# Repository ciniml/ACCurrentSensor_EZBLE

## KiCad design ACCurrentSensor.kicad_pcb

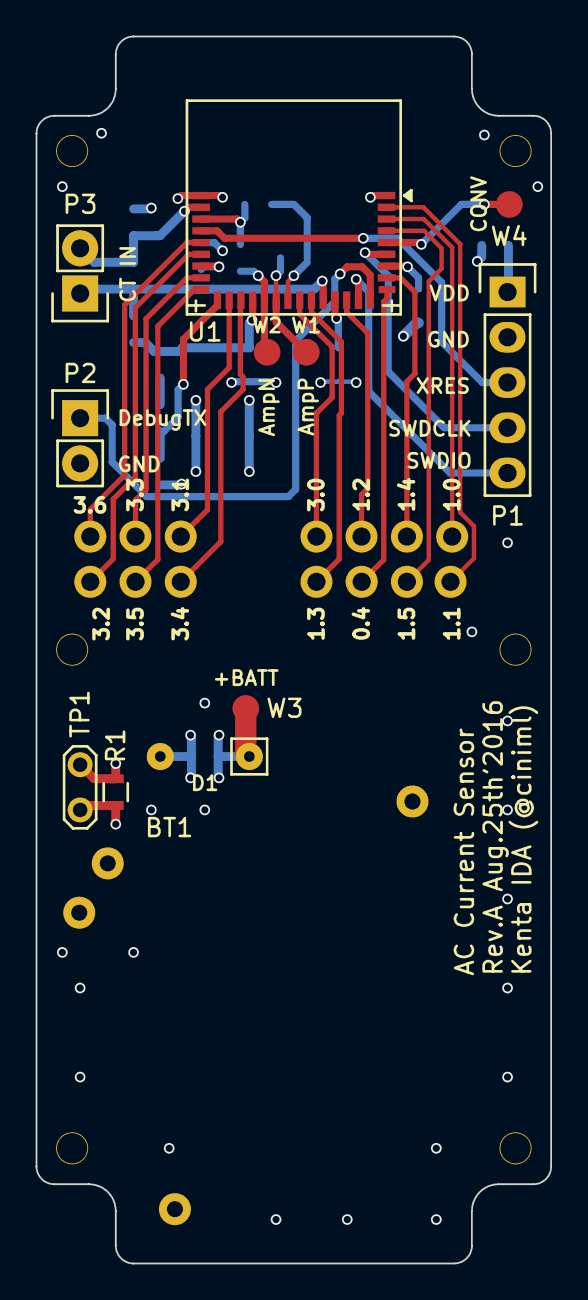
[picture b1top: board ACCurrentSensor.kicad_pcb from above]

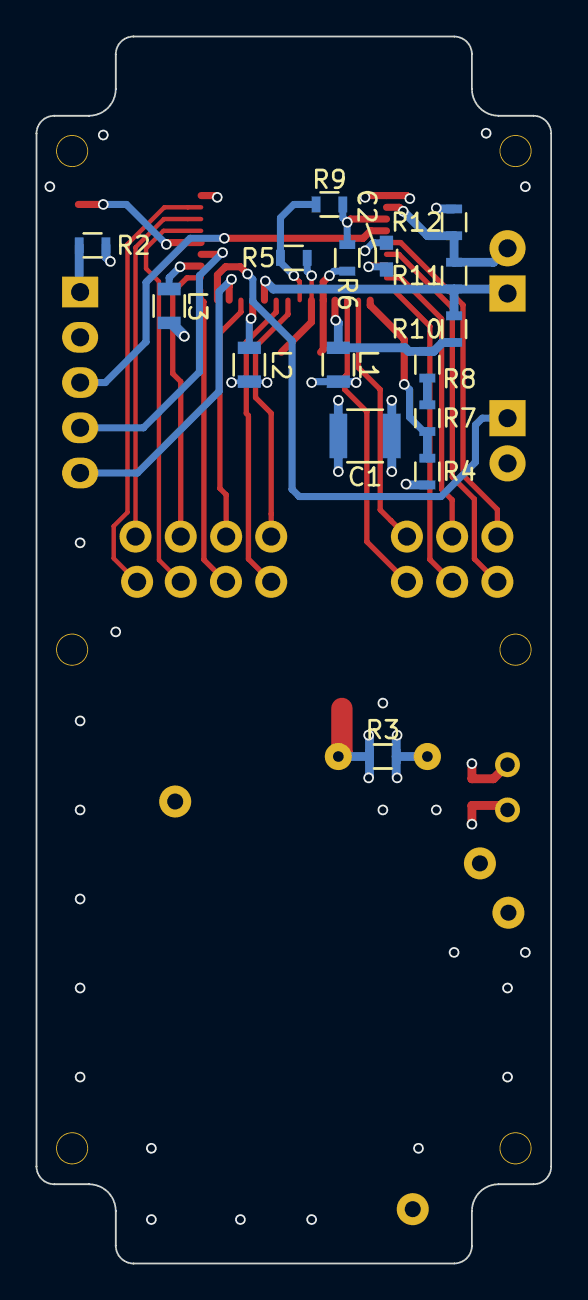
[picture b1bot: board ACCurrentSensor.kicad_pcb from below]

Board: 4 copper layers, 28.9 x 68.9 mm, 42 parts (16 on the bottom side), 36 nets.

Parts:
BT1: Battery; CSPB-75
C1: 100u; C_1210
C2: 100n; C_0603
D1: E-452; CRD-E
L1, L2, L3: BLM21PG331SN; R_0805
P1: PROG; Pin_Header_Straight_1x05
P2: DEBUG_TX; Pin_Header_Straight_1x02
P3: CT; Pin_Header_Straight_1x02
P4, P5, P6, P7, P8, P9, P10, P11, P12, P13, P14, P15, P16, P17: CONN_01X01; OptionalPad_TH
R1, R2, R3: 0R; R_0603
R4, R7, R8, R10, R12: 100k; R_0603
R5, R6: 10k; R_0603
R9: 2k; R_0603
R11: 10; R_0603
TP1: CURRENT; Test_Point_2Pads
U1: CYBLE-014008-00
W1: SENSE_OUT_P; Measurement_Point_Round-SMD-Pad_Small
W2: SENSE_OUT_N; Measurement_Point_Round-SMD-Pad_Small
W3: BATT; Measurement_Point_Round-SMD-Pad_Small
W4: CONVERTED; Measurement_Point_Round-SMD-Pad_Small

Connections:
+BATT: C1.1, D1.K, L1.1, L2.1, L3.1, R2.2, R3.2, W3.1
/BATTREF: R4.2, R7.2, U1.23
/CONVERTED: U1.5, W4.1
/DebugTX: P2.1, U1.10
/OA_H_N: R5.1, R9.2, U1.17
/OA_H_OUT: R5.2, U1.18, W1.1
/OA_H_P: P3.1, R10.1, R11.2, U1.14
/OA_L_N: P3.2, R11.1, R12.2, U1.31
/OA_L_OUT: R6.2, U1.19, W2.1
/OA_L_P: R6.1, R9.1, U1.30
/PIN_0.4: P8.1, U1.9
/PIN_1.0: P5.1, U1.3
/PIN_1.1: P4.1, U1.2
/PIN_1.2: P9.1, U1.12
/PIN_1.3: P10.1, U1.15
/PIN_1.4: P7.1, U1.8
/PIN_1.5: P6.1, U1.4
/PIN_3.0: P11.1, U1.16
/PIN_3.1: P13.1, U1.22
/PIN_3.2: P17.1, U1.27
/PIN_3.3: P14.1, U1.25
/PIN_3.4: P12.1, U1.21
/PIN_3.5: P15.1, U1.24
/PIN_3.6: P16.1, U1.28
/SWDCLK: P1.4, U1.6
/SWDIO: P1.5, U1.11
/XRES: P1.3, U1.29
GND: BT1.2, C1.2, C2.2, P1.2, P2.2, R4.1, R12.1, U1.1, U1.32
unnamed: BT1.1, R1.1, TP1.1
unnamed: C2.1, U1.26
unnamed: D1.A, R1.2, R3.1, TP1.2
unnamed: L2.2, U1.13
unnamed: P1.1, R2.1
unnamed: R7.1, R8.2
VDD: L3.2, U1.7
VDDA: L1.2, R8.1, R10.2, U1.20

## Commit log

2016-07-04 Rename to heater controller
2016-07-20 Finished to design circuit.
2016-08-08 Add terminal components
2016-08-20 configure libraries
2016-08-20 Squashed 'Cypress_BLE/' changes from 074c39c..7f34cae
    7f34cae Merge commit 'f079b8f67eadc266b7d904efed57cf209607fdc3'
    git-subtree-dir: Cypress_BLE
    git-subtree-split: 7f34caed656f73a38f19210eac83beb2f972ae62
2016-08-21 Draw except power circuits.
2016-08-21 Squashed 'akiduki/' changes from e45bb9e..3c22a81
    3c22a81 Merge branch 'subtree_akiduki' of ../ReflowOven_PSoC
    3edb481 Add an ignored component library
    git-subtree-dir: akiduki
    git-subtree-split: 3c22a81959916de3ed027999797e26649687e340
2016-09-27 Revision A
